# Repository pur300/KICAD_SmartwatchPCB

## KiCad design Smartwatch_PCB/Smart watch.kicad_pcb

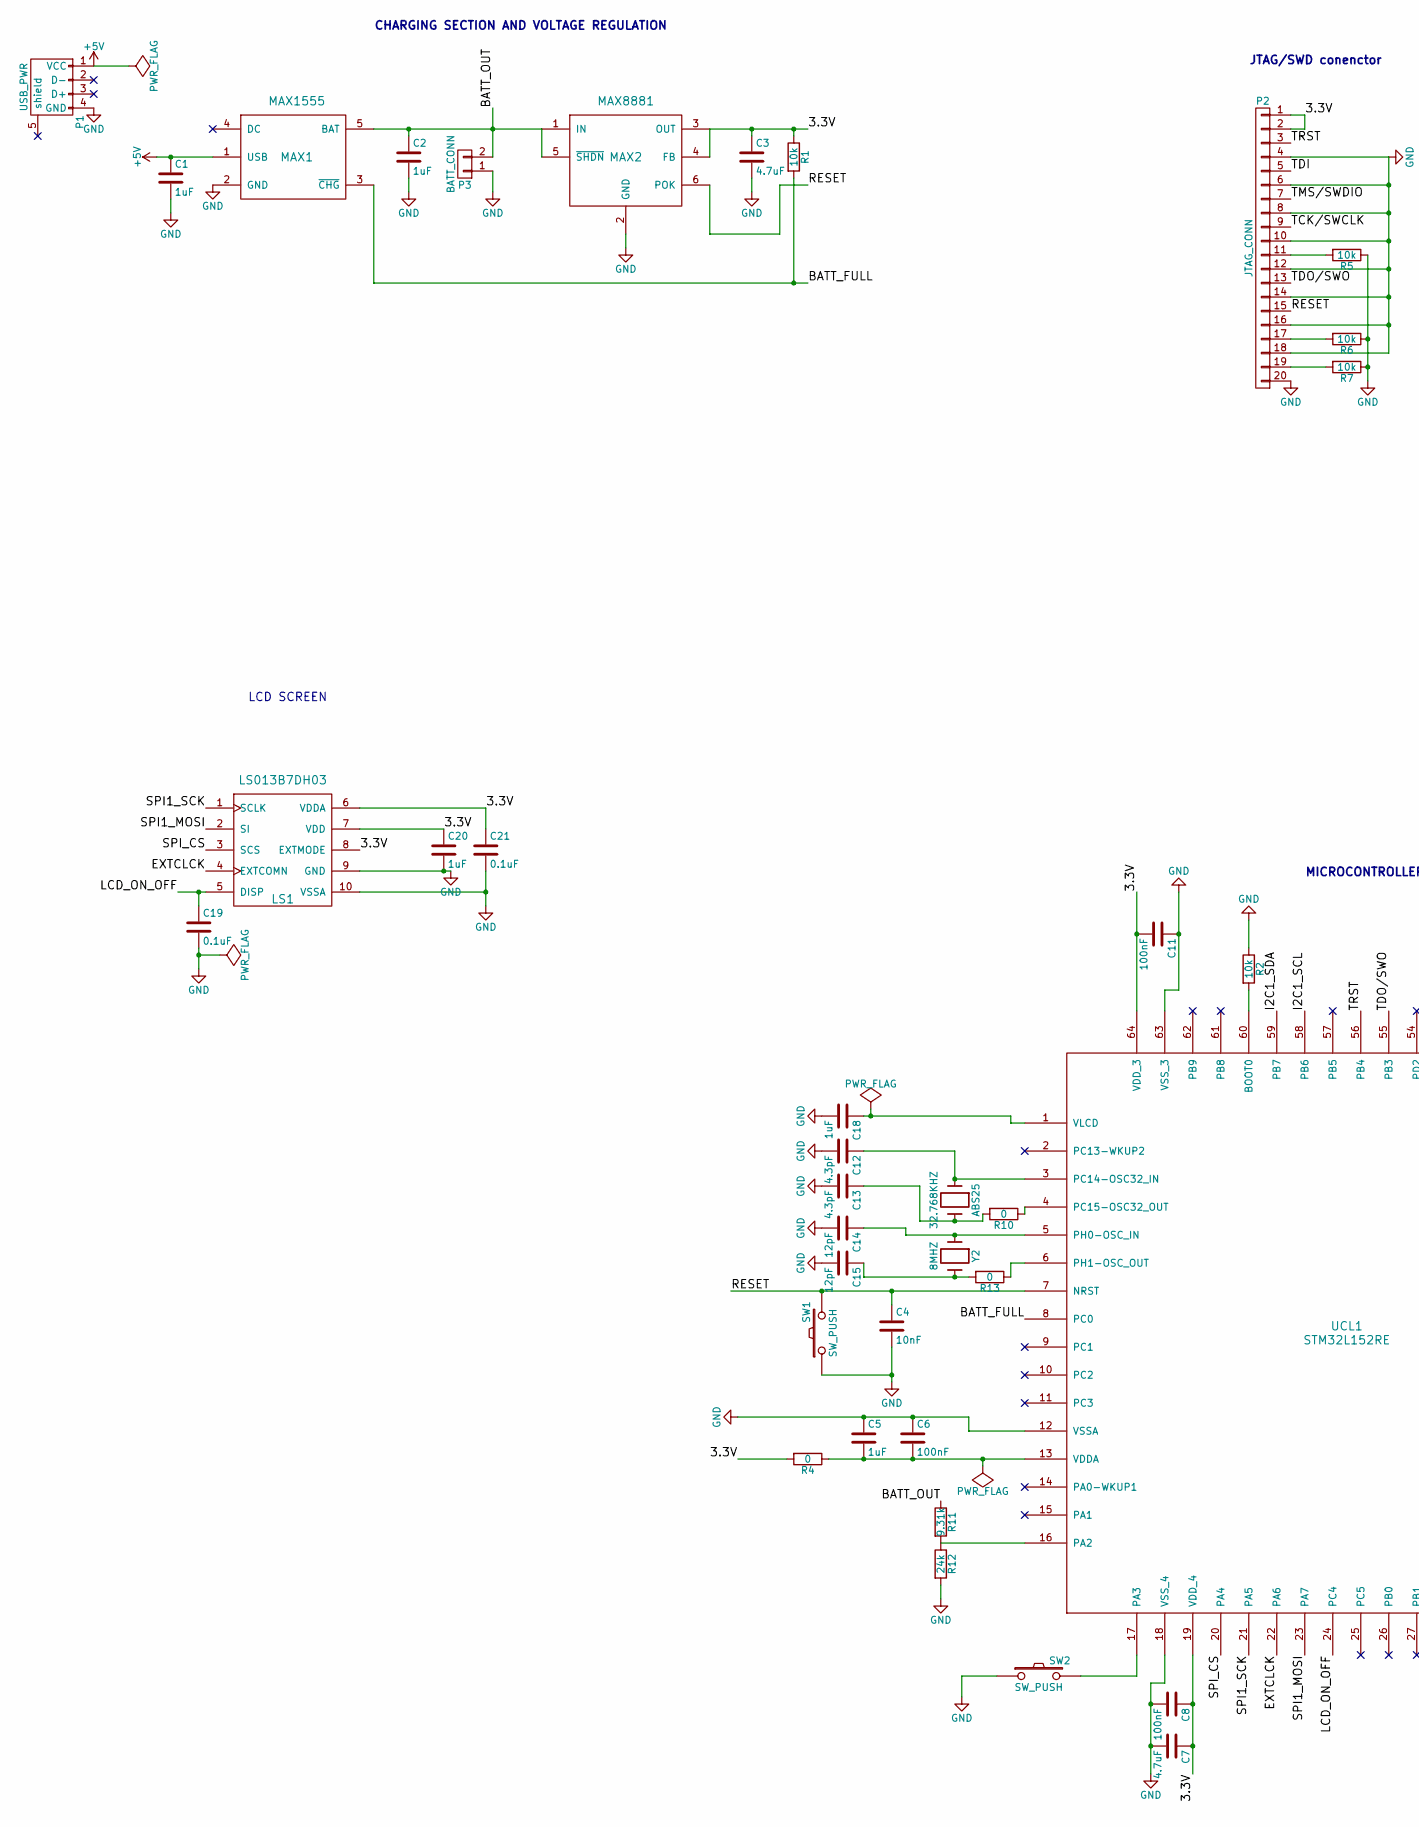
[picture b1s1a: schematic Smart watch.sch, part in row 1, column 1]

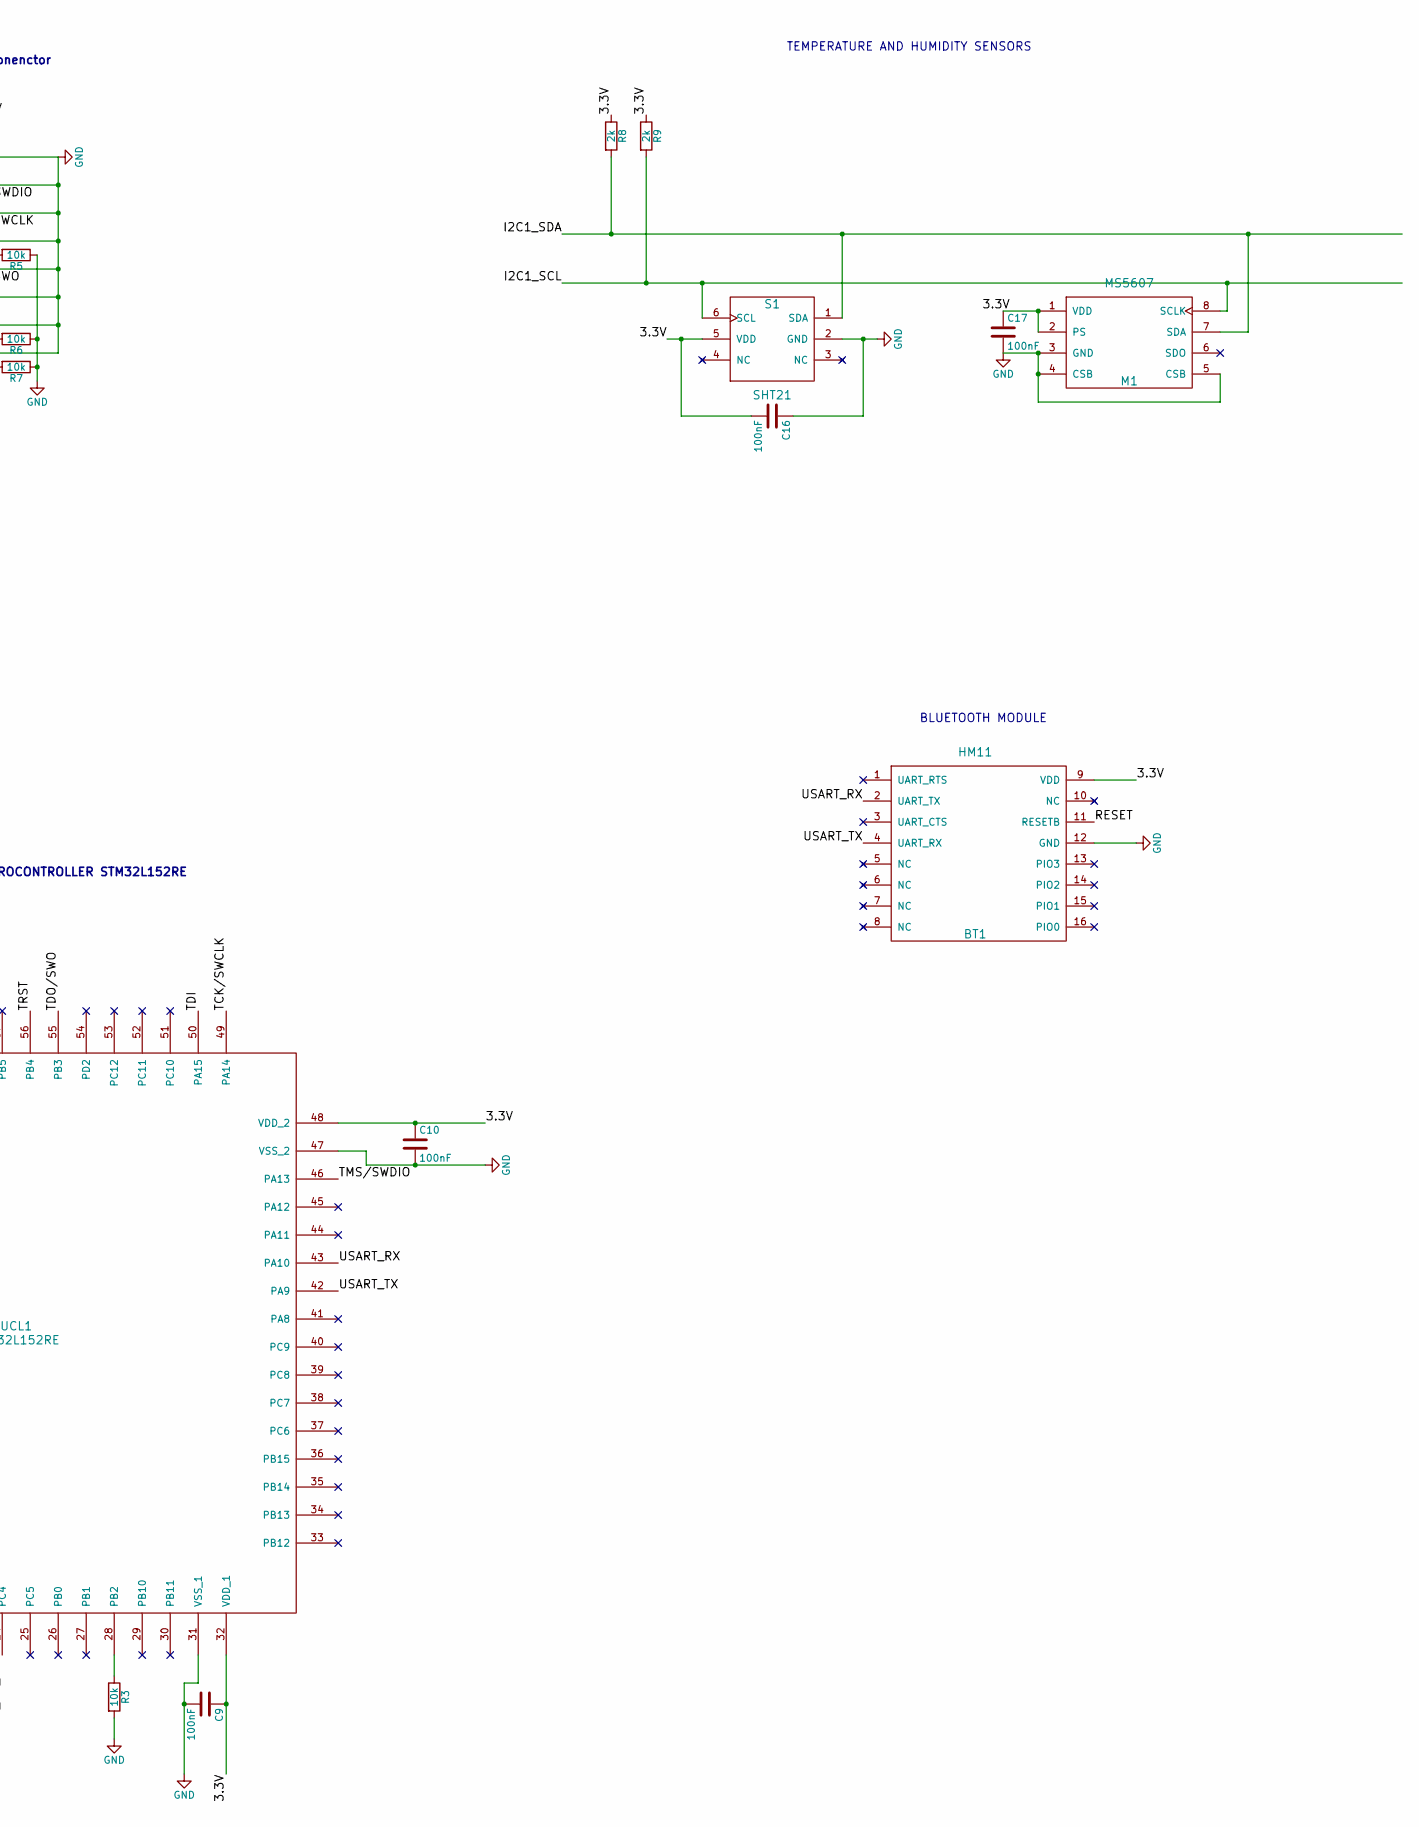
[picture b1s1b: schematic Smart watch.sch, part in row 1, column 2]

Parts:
ABS25: 32.768KHZ; abs25_crystall_smd
BT1: HM11; HM
C1, C2, C5, C18, C20: 1uF; C_0805_HandSoldering
C3, C7: 4.7uF; C_0805_HandSoldering
C4: 10nF; C_0805_HandSoldering
C6, C8, C9, C10, C11, C16, C17: 100nF; C_0805_HandSoldering
C12, C13: 4.3pF; C_0805_HandSoldering
C14, C15: 12pF; C_0805_HandSoldering
C19, C21: 0.1uF; C_0805_HandSoldering
LS1: LS013B7DH03; FPC
M1: MS5607; MEAS
MAX1: MAX1555; SOT23-5-thin
MAX2: MAX8881; SOT23-6
P1: USB_PWR; AB2_USB_MINI_SMD
P2: JTAG_CONN; Socket_Strip_Straight_2x10
P3: BATT_CONN; kk100_22-23-2021
R1, R2, R3, R5, R6, R7: 10k; R_0805_HandSoldering
R4, R10, R13: 0; R_0805_HandSoldering
R8, R9: 2k; R_0805_HandSoldering
R11: 9.31k; R_0805_HandSoldering
R12: 24k; R_0805_HandSoldering
S1: SHT21; DFN
SW1, SW2: SW_PUSH; SW_PUSH_SMALL
UCL1: STM32L152RE; LQFP64
Y2: 8MHZ; Crystal_HC49-SD_SMD

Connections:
+5V: C1.1, MAX1.1 (USB), P1.1 (VCC)
/3.3V: BT1.9 (VDD), C3.1, C7.1, C8.1, C9.1, C10.1, C11.2, C16.2, C17.1, C20.1, C21.1, LS1.6 (VDDA), LS1.7 (VDD), LS1.8 (EXTMODE), M1.1 (VDD), M1.2 (PS), MAX2.3 (OUT), MAX2.4 (FB), P2.1, P2.2, R1.1, R4.2, R8.1, R9.1, S1.5 (VDD), UCL1.19 (VDD_4), UCL1.32 (VDD_1), UCL1.48 (VDD_2), UCL1.64 (VDD_3)
/BATT_FULL: MAX1.3 (~CHG), R1.2, UCL1.8 (PC0)
/BATT_OUT: C2.1, MAX1.5 (BAT), MAX2.1 (IN), MAX2.5 (~SHDN), P3.2, R11.1
/EXTCLCK: LS1.4 (EXTCOMN), UCL1.22 (PA6)
/I2C1_SCL: M1.8 (SCLK), R9.2, S1.6 (SCL), UCL1.58 (PB6)
/I2C1_SDA: M1.7 (SDA), R8.2, S1.1 (SDA), UCL1.59 (PB7)
/LCD_ON_OFF: C19.1, LS1.5 (DISP), UCL1.24 (PC4)
/RESET: BT1.11 (RESETB), C4.1, MAX2.6 (POK), P2.15, SW1.2, UCL1.7 (NRST)
/SPI1_MOSI: LS1.2 (SI), UCL1.23 (PA7)
/SPI1_SCK: LS1.1 (SCLK), UCL1.21 (PA5)
/SPI_CS: LS1.3 (SCS), UCL1.20 (PA4)
/TCK/SWCLK: P2.9, UCL1.49 (PA14)
/TDI: P2.5, UCL1.50 (PA15)
/TDO/SWO: P2.13, UCL1.55 (PB3)
/TMS/SWDIO: P2.7, UCL1.46 (PA13)
/TRST: P2.3, UCL1.56 (PB4)
/USART_RX: BT1.2 (UART_TX), UCL1.43 (PA10)
/USART_TX: BT1.4 (UART_RX), UCL1.42 (PA9)
GND: BT1.12 (GND), C1.2, C2.2, C3.2, C4.2, C5.1, C6.1, C7.2, C8.2, C9.2, C10.2, C11.1, C12.2, C13.2, C14.2, C15.2, C16.1, C17.2, C18.2, C19.2, C20.2, C21.2, LS1.9 (GND), LS1.10 (VSSA), M1.3 (GND), M1.4 (CSB), M1.5 (CSB), MAX1.2 (GND), MAX2.2 (GND), P1.4 (GND), P2.4, P2.6, P2.8, P2.10, P2.12, P2.14, P2.16, P2.18, P2.20, P3.1, R2.1, R3.2, R5.1, R6.1, R7.1, R12.2, S1.2 (GND), SW1.1, SW2.1, UCL1.12 (VSSA), UCL1.18 (VSS_4), UCL1.31 (VSS_1), UCL1.47 (VSS_2), UCL1.63 (VSS_3)
unnamed: ABS25.1, C12.1, UCL1.3 (PC14-OSC32_IN)
unnamed: ABS25.2, C13.1, R10.2
unnamed: C5.2, C6.2, R4.1, UCL1.13 (VDDA)
unnamed: C14.1, UCL1.5 (PH0-OSC_IN), Y2.1
unnamed: C15.1, R13.2, Y2.2
unnamed: C18.1, UCL1.1 (VLCD)
unnamed: P2.11, R5.2
unnamed: P2.17, R6.2
unnamed: P2.19, R7.2
unnamed: R2.2, UCL1.60 (BOOT0)
unnamed: R3.1, UCL1.28 (PB2)
unnamed: R10.1, UCL1.4 (PC15-OSC32_OUT)
unnamed: R11.2, R12.1, UCL1.16 (PA2)
unnamed: R13.1, UCL1.6 (PH1-OSC_OUT)
unnamed: SW2.2, UCL1.17 (PA3)

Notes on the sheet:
MICROCONTROLLER STM32L152RE
CHARGING SECTION AND VOLTAGE REGULATION
JTAG/SWD conenctor
TEMPERATURE AND HUMIDITY SENSORS
BLUETOOTH MODULE
LCD SCREEN

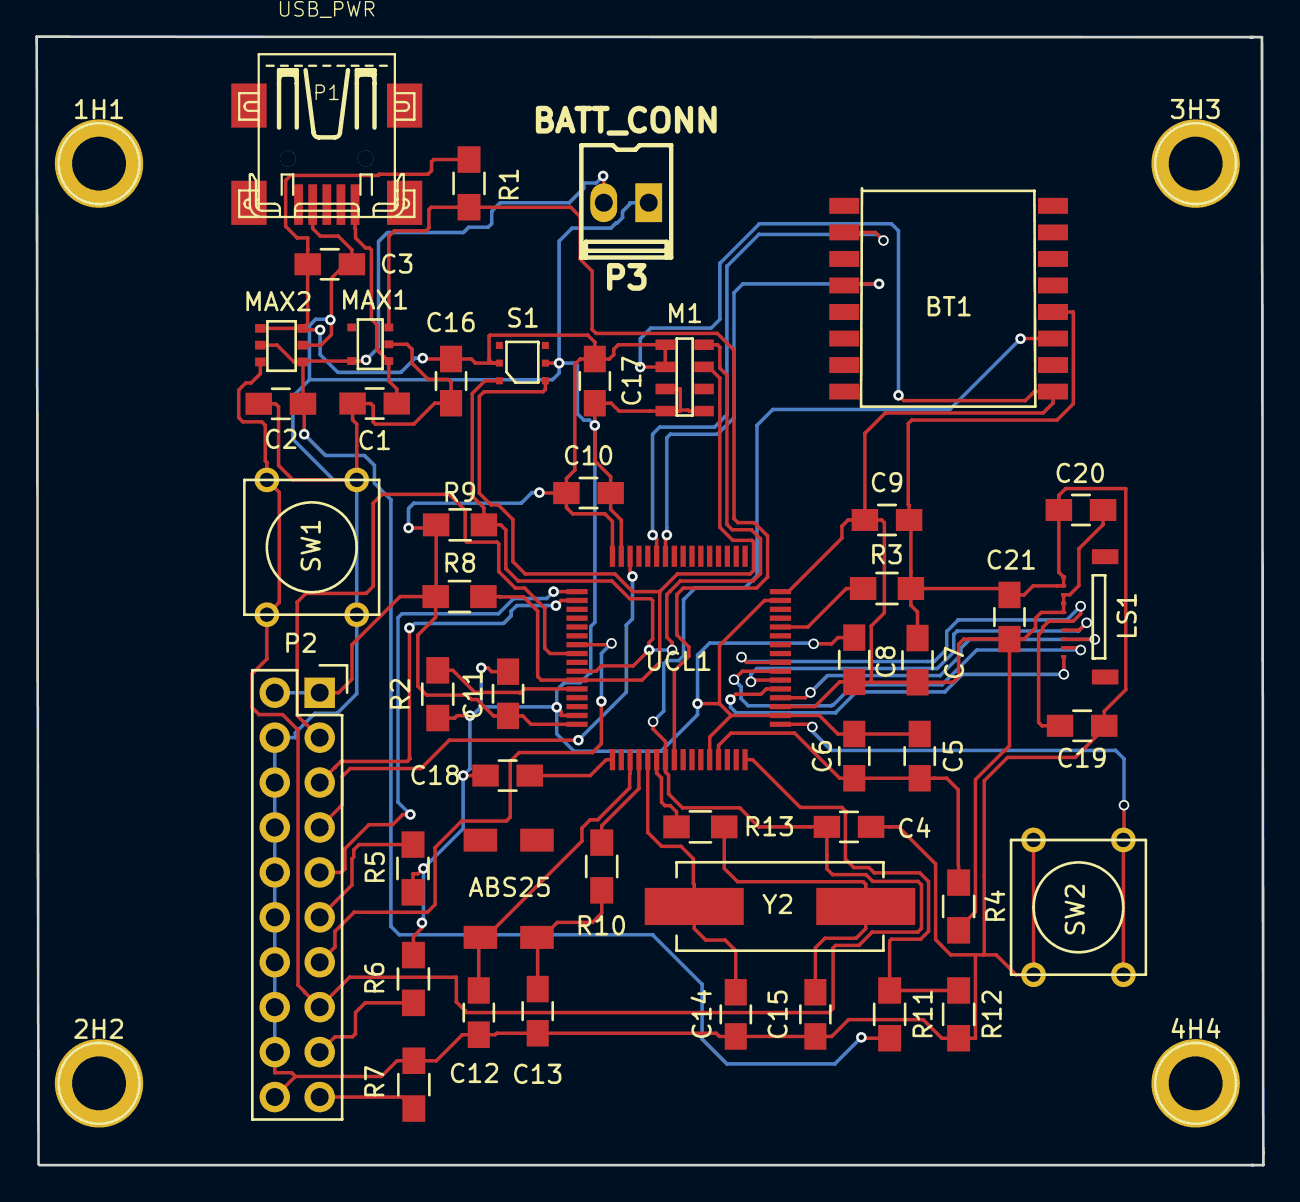
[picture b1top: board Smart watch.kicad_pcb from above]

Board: 2 copper layers, 69.3 x 63.8 mm, 52 parts (0 on the bottom side), 35 nets.

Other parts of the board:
1H1, 2H2, 3H3, 4H4: 1pin

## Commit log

2015-12-03 Smartwatch PCB
2016-01-02 Final version...I hope
